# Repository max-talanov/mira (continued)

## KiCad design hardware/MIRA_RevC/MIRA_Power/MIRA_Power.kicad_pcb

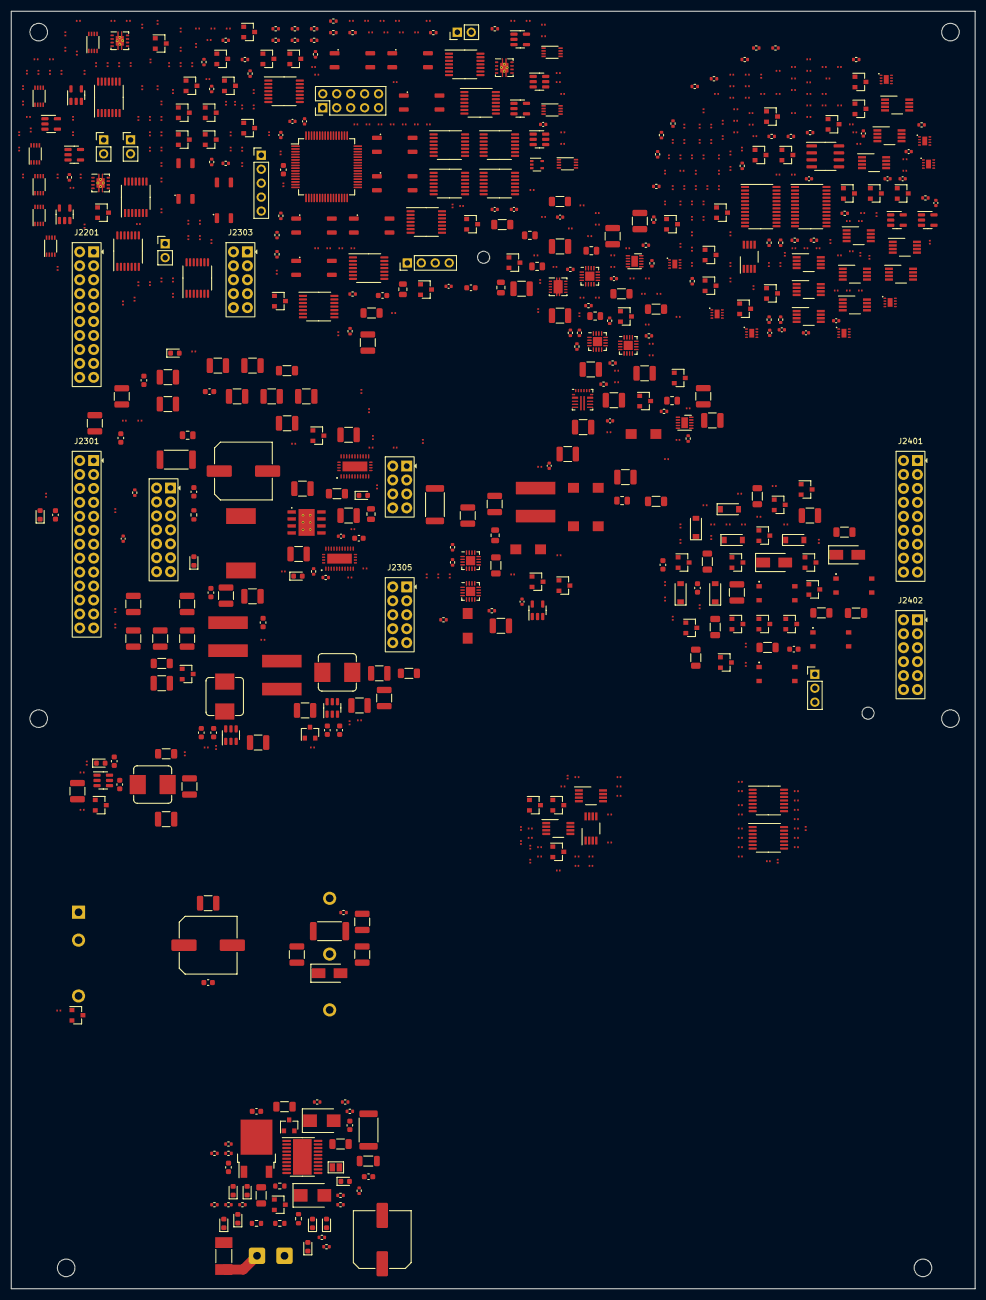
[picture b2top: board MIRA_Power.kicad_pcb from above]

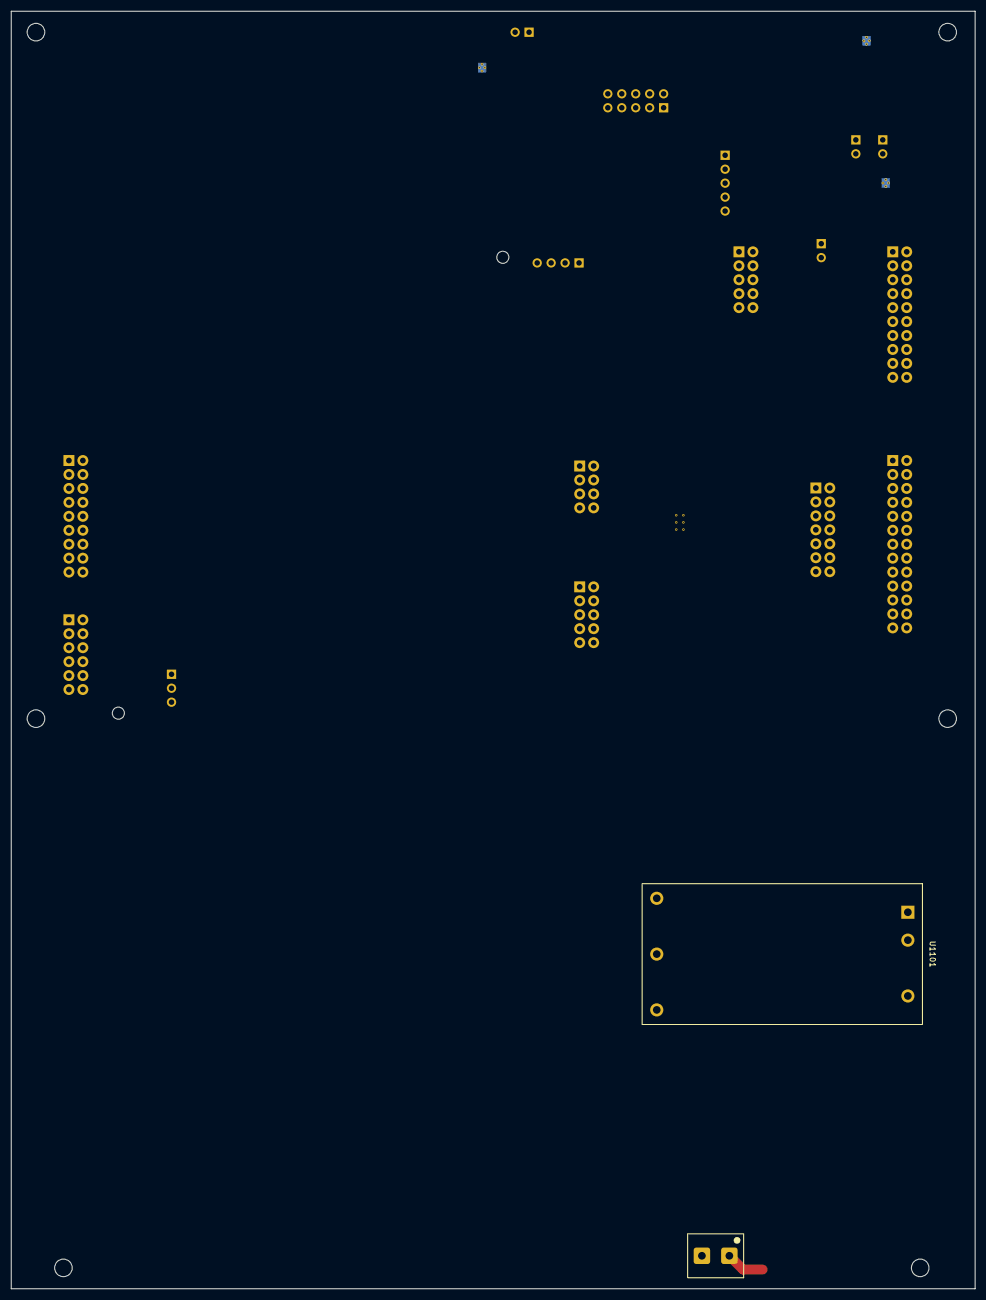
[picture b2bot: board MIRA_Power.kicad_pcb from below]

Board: 4 copper layers, 175.5 x 232.6 mm, 801 parts (2 on the bottom side), 403 nets.

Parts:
C301, C303, C304, C307, C501, C503, C604, C605, C705, C813, C902, C903, C1005, C1006, C1102, C1901, C2001, C2101: 100n; C_0603_1608Metric
C302, C305, C306: 1u; C_1206_3216Metric
C308, C1010, C1106: 100u; C_Elec_10x10.2
C502, C601, C707, C708, C802, C808, C904, C1004, C1008, C1101, C1903, C2003: 4.7u; C_1210_3225Metric
C504, C505, C602, C603, C702, C709, C710, C711, C712, C713, C804, C806, C807, C809, C812, C814, C901, C905, C1301, C1303, C1304, C1306, C1307, C1308, C1309, C1311, C1401, C1408, C1412, C1503, C1602, C1701, C1703, C1706, C1708: 47u; C_1210_3225Metric
C701, C811, C2603: 1u; C_0402_1005Metric
C703, C805, C1305: 22n; C_0201_Murata_GRM03_Gap0.25
C704, C803: 2.2u; C_0603_1608Metric
C706, C801: 150p; C_0201_Murata_GRM03_Gap0.25
C714, C810: 470n; C_0603_1608Metric
C1001: 220n; C_0805_2012Metric
C1002, C1003, C1007: 10u; C_1210_3225Metric
C1009: 1u; C_0805_2012Metric
C1103, C1104, C1105: 22u; C_1210_3225Metric
C1302, C1511, C2601: 4.7u; C_0603_1608Metric
C1310, C1312, C1403, C1405, C1409, C1501, C1601, C2201, C2901, C2902, C3701, C4401, C4901, C4902, C4903, C4904, C5001, C5002, C5003, C5004, C5101: 100n; C_0402_1005Metric
C1402, C1406, C1411, C1504, C1603, C1702, C1705, C2703, C3801, C3803, C3804, C3805, C4101, C4202, C4501, C4502, C4504, C4506, C4508, C4509, C4511, C4512, C4601, C4602, C4603, C4604, C4605, C4608, C4701, C4702, C4704, C4705, C4707, C4708, C4711, C4712, C4801, C4802, C4803, C4805, C4806, C4809, C4810, C4812: 10n; C_0201_Murata_GRM03_Gap0.25
C1404, C1407, C1410, C1502, C1505, C1506, C1507, C1508, C1604: 10u; C_0805_2012Metric
C1509, C1510, C1704, C1707, C2602, C2604, C2605, C2701, C2702, C2801, C2802, C2803, C2804, C2805, C3001, C3002, C3003, C3101, C3102, C3103, C3201, C3202, C3301, C3302, C3401, C3402, C3403, C3404, C3405, C3406, C3407, C3408, C3802, C3901, C3902, C3903, C4001, C4002, C4003, C4102, C4201, C4402, C4403, C4404, C4503, C4505, C4507, C4510, C4606, C4607, C4609, C4703, C4706, C4709, C4710, C4804, C4807, C4808, C4811, C5201, C5202, C5303: 100n; C_0201_Murata_GRM03_Gap0.25
C1902, C2002: 47n; C_1206_3216Metric
C5301, C5302: 1n; C_0201_Murata_GRM03_Gap0.25
D301, D305, D310, D501, D601, D701, D801, D901, D1001: Green LED; LED_0603_1608Metric
D302, D304, D308: Red LED; LED_0603_1608Metric
D303, D307: CD0603-B0240R; D_0603_1608Metric
D306: SMBJ36CA; D_SMB
D309: STPS3H100U; D_SMB
D1101: SS14-13-F; D_SMA
D1901, D2004: SS14 OUTPUT CLAMP; D_SMA
D1902, D1903, D1904, D2001, D2002, D2003: 10V G-S CLAMP; D_SOD-123
D2101: BAT54S ADC CLAMP; SOT-23
D2701: BAT54A; SOT-23
D4201, D4401, D4402, D4403, D4501, D4502, D4503, D4504, D4601, D4602, D4603, D4701, D4702, D4703, D4704, D4801, D4802, D4803, D4804: BAT54S; SOT-23
F301: 5A / 125V; Fuse_Littelfuse_0451_2410_Mfr
H9101, H9102, H9103, H9104, H9301, H9302: M3 support 12mm hardware TBD
H9201, H9202: M2 support12mm under module
J301: DG126-5.0-02P-14; TerminalBlock_Degson_DG126-5.0-02P-14_1x02_P5.00mm
J2101: PROGRAM +/-15V; PinHeader_1x03_P2.54mm_Vertical
J2201: SSW-110-01-S-D; Samtec_SSW-110-01-S-D_2x10_P2.54mm_Vertical
J2301: SSW-113-01-S-D; Samtec_SSW-113-01-S-D_2x13_P2.54mm_Vertical
J2302: SSW-107-01-S-D; Samtec_SSW-107-01-S-D_2x07_P2.54mm_Vertical
J2303, J2305: SSW-105-01-S-D; Samtec_SSW-105-01-S-D_2x05_P2.54mm_Vertical
J2304: SSW-104-01-S-D; Samtec_SSW-104-01-S-D_2x04_P2.54mm_Vertical
J2401: SSW-109-01-S-D; Samtec_SSW-109-01-S-D_2x09_P2.54mm_Vertical
J2402: SSW-106-01-S-D; Samtec_SSW-106-01-S-D_2x06_P2.54mm_Vertical
J2701: HOST MANUAL RESET CONTACT; PinHeader_1x02_P2.54mm_Vertical
J2702: PM MANUAL RESET CONTACT; PinHeader_1x02_P2.54mm_Vertical
J3101: MATRIX STOP - CLOSE TO TRIP; PinHeader_1x02_P2.54mm_Vertical
J3102: GLOBAL STOP - CLOSE TO TRIP; PinHeader_1x02_P2.54mm_Vertical
J3103: MATRIX HARDWARE INTERLOCK - AON LOGIC; PinHeader_1x04_P2.54mm_Vertical
J4201: PM SWD - VTREF ONLY; PinHeader_1x05_P2.54mm_Vertical
J4202: MAIN CONTROLLER UART / WATCHDOG / STATUS; PinHeader_2x05_P2.54mm_Vertical
JP301: SolderJumper_2_Open; SolderJumper-2_P1.3mm_Open_Pad1.0x1.5mm
L301: 120R @ 100MHz / 6A; L_1206_3216Metric
L501, L601, L901: 33uH; L_Bourns_SRP7028A_7.3x6.6mm
L701, L801: 6.8uH; L_Bourns_SRP7030CA_7.8x7.6mm
L1001: 47u; L_Wurth_7447709101_12x12mm
L1301: 1u; L_Bourns_SRP7030CA_7.8x7.6mm
L1401, L1402, L1403, L1501, L1601: 2.2u; L_Bourns_SRP5030TA_5.7x5.2mm
Q301, Q302, Q601, Q701, Q801, Q901, Q1101, Q1301, Q1401, Q1402, Q1403, Q1501, Q1601, Q1701, Q1702, Q3101, Q3102: BSS138N; SOT-23
Q303: IRFR3410; TO-252-2
Q1901, Q1904, Q1906, Q2001: AO3401A; SOT-23
Q1902, Q1903, Q1905, Q1907, Q2002, Q2003, Q2004, Q3501, Q3502, Q3503, Q3504, Q3505, Q3601, Q3602, Q3603, Q3604, Q3605: AO3400A; SOT-23
R301, R303, R305, R317, R1004: 10k; R_0603_1608Metric
R302, R309, R311, R4402, R4404, R4408: 10k; R_0402_1005Metric
R304, R3502, R3504, R3506, R3508, R3510, R3602, R3604, R3606, R3608, R3610: 22k; R_0402_1005Metric
R306: 24k; R_0402_1005Metric
R307, R314: 150k; R_0402_1005Metric
R308: 16.2k; R_0402_1005Metric
R310, R313: 180k; R_0402_1005Metric
R312: 12.1k; R_0402_1005Metric
R315: 4.02k; R_0402_1005Metric
R316, R318, R1001, R1005, R1102, R3701, R4409, R4901, R4902, R4903, R4904, R4905, R4906, R4907, R4908, R5001, R5002, R5003, R5004, R5005, R5006, R5007, R5101: 100k; R_0402_1005Metric
R319: 20m / 1W; R_2512_6332Metric
R501: 62k; R_0201_Panasonic_ERJ1G_Gap0.30
R502, R601, R703, R801, R901, R4203, R4205, R4511, R4512, R4514, R4516, R4601, R4604, R4611, R4701, R4711, R4714, R4715, R4802, R4807, R4812, R4814: 1k; R_0201_Panasonic_ERJ1G_Gap0.30
R503: 0.1R; R_1206_3216Metric
R504, R603, R905: 20k; R_0201_Panasonic_ERJ1G_Gap0.30
R602, R702, R704, R803, R806, R903, R1103, R1305, R1403, R1412, R1414, R1502, R1508, R1605, R1705, R1712, R1901, R1904, R1905, R1908, R2004, R2007, R2008, R2201, R2701, R2706, R2804, R2901, R2902, R2903, R3002, R3004, R3102, R3103, R3104, R3107, R3201, R3202, R3203, R3204, R3205, R3206, R3207, R3208, R3209, R3210, R3211, R3212, R3213, R3214, R3215, R3216, R3301, R3302, R3303, R3304, R3305, R3306, R3307, R3308, R3309, R3310, R3311, R3312, R3313, R3314, R4202, R4206, R4207, R5301, R5304, R5306, R5307, R5308: 100k; R_0201_Panasonic_ERJ1G_Gap0.30
R604, R904, R1703, R1710: 0.05R; R_1206_3216Metric
R605: 105k; R_0201_Panasonic_ERJ1G_Gap0.30
R701, R802, R1301, R1303, R1307, R1402, R1406, R1409, R1411, R1413, R1416, R1505, R1506, R1509, R1603, R1604, R1701, R1706, R1709, R1711, R2101, R2102, R2702, R2703, R2704, R2705, R2707, R2708, R2709, R2801, R2802, R2803, R3101, R3105, R3106, R3413, R3416, R3802, R3803, R3805, R3808, R3809, R3810, R3811, R3812, R4101, R4501, R4502, R4503, R4506, R4507, R4508, R4509, R4510, R4513, R4515, R4602, R4603, R4605, R4607, R4608, R4609, R4612, R4702, R4703, R4704, R4705, R4706, R4707, R4708, R4709, R4710, R4713, R4716, R4801, R4803, R4804, R4805, R4806, R4808, R4809, R4810, R4811, R4813, R4816, R5302: 10k; R_0201_Panasonic_ERJ1G_Gap0.30
R705: 43.2k; R_0201_Panasonic_ERJ1G_Gap0.30
R706, R804, R1504: 0.01R; R_1206_3216Metric
R805: 22.1k; R_0201_Panasonic_ERJ1G_Gap0.30
R902: 130k; R_0201_Panasonic_ERJ1G_Gap0.30
R1002, R1101: 0.1R; R_2512_6332Metric
R1003: 7.15k; R_0402_1005Metric
R1302: 15.0k; R_0402_1005Metric
R1304: 0.002R; R_2512_6332Metric
R1306: 10.2k; R_0402_1005Metric
R1308: 200k; R_0201_Panasonic_ERJ1G_Gap0.30
R1309, R5303, R5305: 100; R_0201_Panasonic_ERJ1G_Gap0.30
R1401: 20.0k; R_0402_1005Metric
R1404, R1408, R1418, R1501, R1601, R1708: 16.0k; R_0402_1005Metric
R1405, R1410, R1415, R1606: 0.02R; R_1206_3216Metric
R1407: 34.0k; R_0402_1005Metric
R1417, R1707: 49.9k; R_0402_1005Metric
R1503: 11.0k; R_0402_1005Metric
R1507, R1510, R4102, R4403, R4405, R4406: 10.0k; R_0402_1005Metric
R1511: 0R; R_0201_Panasonic_ERJ1G_Gap0.30
R1602: 20k; R_0402_1005Metric
R1702: 2.00k; R_0402_1005Metric
R1704: 10.5k; R_0402_1005Metric
R1902, R1907, R1909, R2006, R2009, R2011: 680R; R_1206_3216Metric
R1903, R2002, R2003, R2005: 300; R_0201_Panasonic_ERJ1G_Gap0.30
R1906, R2010: 330k; R_0201_Panasonic_ERJ1G_Gap0.30
R1910, R2001: 1M; R_0201_Panasonic_ERJ1G_Gap0.30
R2103, R3406, R4606: 47k; R_0201_Panasonic_ERJ1G_Gap0.30
R3001: 590k; R_0201_Panasonic_ERJ1G_Gap0.30
R3003: 150k; R_0201_Panasonic_ERJ1G_Gap0.30
R3401, R3402, R3403, R3404, R3405, R3407, R3408, R3409, R3410, R3411, R3412, R3414, R3415: 220k; R_0201_Panasonic_ERJ1G_Gap0.30
R3501, R3503, R3505, R3507, R3509, R3601, R3603, R3605, R3607, R3609: 270; R_0402_1005Metric
R3702: 1k; R_0402_1005Metric
R3801: 4.7k; R_0201_Panasonic_ERJ1G_Gap0.30
R3804: 3.9k; R_0201_Panasonic_ERJ1G_Gap0.30
R3806: 15k; R_0201_Panasonic_ERJ1G_Gap0.30
R3807: 2.2k; R_0201_Panasonic_ERJ1G_Gap0.30
R4103: 2.74k; R_0402_1005Metric
R4201, R4204: 33; R_0201_Panasonic_ERJ1G_Gap0.30
R4401, R4407: 200k; R_0402_1005Metric
R4504, R4505: 75k; R_0201_Panasonic_ERJ1G_Gap0.30
R4610: 30.1k; R_0201_Panasonic_ERJ1G_Gap0.30
R4712: 7.50k; R_0201_Panasonic_ERJ1G_Gap0.30
R4815: 13.7k; R_0201_Panasonic_ERJ1G_Gap0.30
U301: TPS26631PWPR; HTSSOP-20-1EP_4.4x6.5mm_P0.65mm_EP3.4x6.5mm_Mask2.96x2.96mm
U501, U601, U901: LMR51610XDBVR; SOT-23-6
U701, U801: LM76005RNPR; TI_LM76005_RNP0030G
U1001: LMR36520FADDAR; TI_DDA0008B
U1101: ECB40W18-72S15N; Cincon_ECB40W18_no_bus
U1301: TPS568215RNNR; Texas_RNN0018A
U1401, U1402, U1403, U1501, U1601: TPS62130ARGTR; VQFN-16-1EP_3x3mm_P0.5mm_EP1.68x1.68mm
U1502: TPS51200DRCR; Texas_DRC0010J
U1701, U1702: TPS7A9101DSKR; WSON-10-1EP_2.5x2.5mm_P0.5mm_EP1.2x2mm
U1901, U2001, U2002, U2003: LTV-356T-A; LTV356T_SOP4_P2.54mm_Mfr
U2201, U2901, U2902, U5101: 74LVC1G17GV,125; SOT-23-5
U2601: STM32G0B1RBT6; LQFP-64_10x10mm_P0.5mm
U2701, U2702, U2801: TPS3851H33EDRBR; Texas_DRB0008A
U2802: 74LVC1G14GV; SOT-23-5
U2803, U3003: 74LVC1G08GV; SOT-23-5
U2804: SN74LVC1G74DCUR; VSSOP-8_2.3x2mm_P0.5mm
U2805: SN74LVC1G07DBVR; SOT-23-5
U3001: TPS3808G01DBVR; SOT-23-6
U3002: 74AUP1G34GW; SOT-353_SC-70-5
U3101, U3103, U3901, U3902, U3903, U4001, U4002, U4003: SN74HCS21PWR; TSSOP-14_4.4x5mm_P0.65mm
U3102: SN74HC74PWR; TSSOP-14_4.4x5mm_P0.65mm
U3201, U3202, U3301, U3302: SN74HC08PWR; TSSOP-14_4.4x5mm_P0.65mm
U3401, U3402, U3403, U3404, U3405, U3406, U3407, U3408: 74AUP2G126DC; VSSOP-8_2.3x2mm_P0.5mm
U3501, U3502, U3503, U3504, U3505, U3601, U3602, U3603, U3604, U3605: TLP172GM(TPR,E); SO6_4Pin_Toshiba_11-4M1S
U3701: SN74LVC1G11; SOT-23-6
U3801, U4101: TLV1704AIPWR; TSSOP-14_4.4x5mm_P0.65mm
U4201: 74LVC125APW,118; TSSOP-14_4.4x5mm_P0.65mm
U4401: OPA2991IDR; SOIC-8_3.9x4.9mm_P1.27mm
U4501, U4502, U4504, U4601, U4602, U4603, U4702, U4703, U4704, U4801, U4802, U4804: INA301A1IDGKR; VSSOP-8_3.0x3.0mm_P0.65mm
U4503: INA293A1IDBVR; SOT-23-5
U4701, U4803: INA301A2IDGKR; VSSOP-8_3.0x3.0mm_P0.65mm
U4901, U4902, U4903, U4904, U5001, U5002, U5003, U5004: TMUX2821DSGR; WSON-8_2x2mm_P0.5mm_EP0.9x1.6mm
U5201, U5202: CD74HC4067PWR; TSSOP-24_4.4x7.8mm_P0.65mm
U5301: TLV9002IDGKR; VSSOP-8_3.0x3.0mm_P0.65mm

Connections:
+24V_FUSED: C301.2, C305.1, D306.2 (A2), F301.2, Q302.2 (S), Q303.3 (S), R304.1, R305.2, R313.2, U301.6 (IN_SYS)
+24V_RAW: F301.1, J301.1, R301.2, R303.1
/Power Distribution/Power Sequencing/Command Ready/CMD_GROUP_0: U4001.1 (1A), U4002.6 (1Y)
/Power Distribution/Power Sequencing/Command Ready/CMD_GROUP_1: U4001.2 (1B), U4002.8 (2Y)
/Power Distribution/Power Sequencing/Command Ready/CMD_GROUP_2: U4001.4 (1C), U4003.6 (1Y)
/Power Distribution/Power Sequencing/Command Ready/CMD_GROUP_3: U4001.5 (1D), U4003.8 (2Y)
/Power Distribution/Power Sequencing/Permit Interlocks/INPUT_AON_OK: U3101.6 (1Y), U3101.9 (2A)
/Power Distribution/Power Sequencing/Permit Interlocks/MATRIX_BASE_OK: U3103.6 (1Y), U3103.9 (2A)
/Power Distribution/Power Sequencing/Permit Interlocks/MATRIX_CLEAR_N: U3102.13 (2CLR_N), U3103.8 (2Y)
/Power Distribution/Power Sequencing/Rail Ready/PG_GROUP_0: U3901.6 (1Y), U3903.1 (1A)
/Power Distribution/Power Sequencing/Rail Ready/PG_GROUP_1: U3901.8 (2Y), U3903.2 (1B)
/Power Distribution/Power Sequencing/Rail Ready/PG_GROUP_2: U3902.6 (1Y), U3903.4 (1C)
/Power Distribution/Power Sequencing/Rail Ready/PG_GROUP_3: U3902.8 (2Y), U3903.5 (1D)
/Power Distribution/Primary Converters/AFE +15 V/CB_P15: C1006.1, U1001.7 (BOOT)
/Power Distribution/Primary Converters/AFE +15 V/FB_P15: R1003.1, R1005.2, U1001.5 (FB)
/Power Distribution/Primary Converters/AFE -15 V/N15_REMOTE_EN: Q1101.3 (D), U1101.6 (REMOTE)
/Power Distribution/Primary Converters/AON 3.3 V/AON_CB: C501.1, U501.1 (CB)
/Power Distribution/Primary Converters/AON 3.3 V/AON_FB: R501.1, R504.2, U501.3 (FB)
/Power Distribution/Primary Converters/Analog 6 V/ANA_CB: C903.1, U901.1 (CB)
/Power Distribution/Primary Converters/Analog 6 V/ANA_FB: R902.1, R905.2, U901.3 (FB)
/Power Distribution/Primary Converters/FPGA 5.5 V/FPGA_FB: C801.1, R805.2, R806.1, U801.12 (FB)
/Power Distribution/Primary Converters/FPGA 5.5 V/FPGA_SW: C810.2, L801.1, U801.1 (SW), U801.2 (SW), U801.3 (SW), U801.4 (SW), U801.5 (SW)
/Power Distribution/Primary Converters/System 3.3 V/SYS_FB: C706.1, R704.1, R705.2, U701.12 (FB)
/Power Distribution/Primary Converters/System 3.3 V/SYS_SW: C714.2, L701.1, U701.1 (SW), U701.2 (SW), U701.3 (SW), U701.4 (SW), U701.5 (SW)
/Power Distribution/Primary Converters/USB 5 V/USB_CB: C605.1, U601.1 (CB)
/Power Distribution/Primary Converters/USB 5 V/USB_FB: R603.2, R605.1, U601.3 (FB)
/Power Distribution/Secondary Converters/Analog LDO Rails/FB_ANA5: C1702.2, R1702.1, R1704.2, U1701.3 (FB)
/Power Distribution/Secondary Converters/Analog LDO Rails/FB_ANA33: C1705.2, R1707.2, R1708.1, U1702.3 (FB)
/Power Distribution/Secondary Converters/DDR Supply and Termination/FB_DDR: R1501.1, R1503.2, U1501.5 (FB)
/Power Distribution/Secondary Converters/FPGA Auxiliary Rails/FB_AUX18: R1401.2, R1404.1, U1401.5 (FB)
/Power Distribution/Secondary Converters/FPGA Auxiliary Rails/FB_AUX25: R1407.2, R1408.1, U1402.5 (FB)
/Power Distribution/Secondary Converters/FPGA Auxiliary Rails/FB_IO33: R1417.2, R1418.1, U1403.5 (FB)
/Power Distribution/Secondary Converters/FPGA Core 1 V/FB_CORE: R1302.1, R1306.2, U1301.13 (FB)
/Power Distribution/Secondary Converters/I-O 1.8 V/FB_IO18: R1601.1, R1602.2, U1601.5 (FB)
ADC_I: C5302.2, R5303.2, U2601.17 (PA0)
ADC_V: C5301.1, R5305.2, U2601.18 (PA1)
ADC_VTT: C4202.1, R4205.2, U5004.1 (S1)
ADC_VTT_SAFE: D4201.3 (K1/A2), R5007.1, U2601.19 (PA2), U5004.2 (D1)
ALL_COMMANDS_ON: U3103.4 (1C), U4001.6 (1Y)
ALL_RAILS_PG: U2601.3 (PC13), U3103.2 (1B), U3903.6 (1Y), U4201.9 (3A)
ALL_RAILS_PG_POWER: J2201.9, J4202.7, U4201.8 (3Y)
ANA3V3: J2402.7, R1709.1, R1710.2, R4813.2, U4802.7 (IN-)
ANA5: C1708.1, J2401.9, J2402.5, Q1702.3 (D), R1701.1, R1703.2, R4809.2, U1702.9 (IN), U1702.10 (IN), U4801.7 (IN-)
ANA5_RAW: C1702.1, C1703.1, R1703.1, R1704.1, U1701.1 (OUT), U1701.2 (OUT), U4801.8 (IN+)
ANA6: C1701.1, Q1701.3 (D), R901.1, R904.2, R4602.2, U1701.9 (IN), U1701.10 (IN), U4602.7 (IN-)
ANA33_RAW: C1705.1, C1706.1, R1707.1, R1710.1, U1702.1 (OUT), U1702.2 (OUT), U4802.8 (IN+)
ANA_RAW: C901.2, C905.2, L901.2, R902.2, R904.1, U4602.8 (IN+)
ANA_SW: C903.2, L901.1, U901.6 (SW)
AON: C1511.1, C2201.1, C2601.1, C2602.1, C2603.1, C2604.1, C2605.1, C2701.1, C2801.1, C2802.1, C2803.1, C2804.1, C2805.1, C2901.1, C2902.1, C3001.1, C3002.1, C3003.1, C3101.1, C3102.1, C3103.1, C3201.1, C3202.1, C3301.1, C3302.1, C3401.1, C3402.1, C3403.1, C3404.1, C3405.1, C3406.1, C3407.1, C3408.1, C3701.1, C3802.1, C3901.1, C3902.1, C3903.1, C4001.1, C4002.1, C4003.1, C4102.1, C4402.1, C4503.1, C4505.1, C4507.1, C4510.1, C4606.1, C4607.1, C4609.1, C4703.1, C4706.1, C4709.1, C4710.1, C4804.1, C4807.1, C4808.1, C4811.1, C4901.1, C4902.1, C4903.1, C4904.1, C5001.1, C5002.1, C5003.1, C5004.1, C5101.1, C5201.1, C5202.1, C5303.1, D2101.2 (K), D4201.2 (K), D4401.2 (K), D4402.2 (K), D4403.2 (K), D4501.2 (K), D4502.2 (K), D4503.2 (K), D4504.2 (K), D4601.2 (K), D4602.2 (K), D4603.2 (K), D4701.2 (K), D4702.2 (K), D4703.2 (K), D4704.2 (K), D4801.2 (K), D4802.2 (K), D4803.2 (K), D4804.2 (K), J2201.19, J2303.7, J2402.11, J3103.3, J4201.1, R309.1, R311.2, R502.1, R503.2, R701.1, R802.1, R1301.2, R1406.2, R1411.2, R1416.2, R1506.2, R1509.2, R1604.2, R1706.2, R1711.2, R1903.1, R2002.1, R2003.1, R2005.1, R2010.1, R2702.2, R2704.2, R2705.2, R2708.2, R2709.2, R2801.1, R2802.1, R2803.1, R3001.1, R3003.1, R3004.1, R3101.2, R3105.2, R3106.2, R3501.1, R3503.1, R3505.1, R3507.1, R3509.1, R3601.1, R3603.1, R3605.1, R3607.1, R3609.1, R3801.1, R3802.2, R3804.1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
AON_MON_ENABLE: R5101.1, U4901.3 (SEL2), U4901.7 (SEL1), U4902.3 (SEL2), U4902.7 (SEL1), U4903.3 (SEL2), U4903.7 (SEL1), U4904.3 (SEL2), U4904.7 (SEL1), U5001.3 (SEL2), U5001.7 (SEL1), U5002.3 (SEL2), U5002.7 (SEL1), U5003.3 (SEL2), U5003.7 (SEL1), U5004.7 (SEL1), U5101.4 (Y)
AON_RAW: C504.2, C505.2, L501.2, R501.2, R503.1, U4504.8 (IN+)
AON_RESET_N: D2701.1 (K1), R2704.1, U2702.8 (RESET_N), U3101.1 (1A)
AON_SW: C501.2, L501.1, U501.6 (SW)
AUX1V8: J2301.19, J2301.21, R1402.1, R1405.2, R4707.2, U4703.7 (IN-)
AUX2V5: R1409.1, R1410.2, R4705.2, U4704.7 (IN-)
AUX18_RAW: C1401.1, L1401.2, R1401.1, R1405.1, U1401.7 (FSW), U1401.14 (VOS), U4703.8 (IN+)
AUX25_RAW: C1408.1, L1402.2, R1407.1, R1410.1, U1402.7 (FSW), U1402.14 (VOS), U4704.8 (IN+)
BUS24: C502.1, C503.1, C601.1, C604.1, C705.2, C707.2, C708.2, C802.2, C808.2, C813.2, C902.1, C904.1, C1001.1, C1004.1, C1008.1, C1101.1, C1102.1, C1106.1, Q601.3 (D), Q701.3 (D), Q801.3 (D), Q901.3 (D), R317.2, R318.2, R319.2, R4504.2, U501.4 (EN), U501.5 (VIN), U601.5 (VIN), U701.20 (PVIN), U701.21 (PVIN), U701.22 (PVIN), U801.20 (PVIN), U801.21 (PVIN), U801.22 (PVIN), U901.5 (VIN), U1001.2 (VIN), U1101.1 (+VIN), U3501.6 (SW1), U3502.6 (SW1), U3503.6 (SW1), U3504.6 (SW1), U3505.6 (SW1), U4503.4 (IN-)
BUS24_PRE_SHUNT: C306.2, C307.2, C308.1, L301.2, R319.1, U4503.3 (IN+)
CMD_ANA: Q901.1 (G), R3404.1, U3402.3 (2Y), U4002.5 (1D)
CMD_ANA5: Q1701.1 (G), R3414.1, U3407.3 (2Y), U4003.10 (2B)
CMD_ANA5_RAW: R3307.1, U3301.6 (2Y), U3407.5 (2A)
CMD_ANA33: Q1702.1 (G), R3415.1, U3408.6 (1Y), U4003.12 (2C)
CMD_ANA33_RAW: R3309.1, U3301.8 (3Y), U3408.2 (1A)
CMD_ANA_RAW: R3205.2, U3201.11 (4Y), U3402.5 (2A)
CMD_AUX18: Q1401.1 (G), R3408.1, U3404.3 (2Y), U4002.13 (2D)
CMD_AUX18_RAW: R3213.2, U3202.11 (4Y), U3404.5 (2A)
CMD_AUX25: Q1402.1 (G), R3409.1, U3405.6 (1Y), U4003.1 (1A)
CMD_AUX25_RAW: R3304.1, U3302.3 (1Y), U3405.2 (1A)
CMD_CORE: Q1301.1 (G), R3407.1, U3404.6 (1Y), U4002.12 (2C)
CMD_CORE_RAW: R3208.1, U3202.8 (3Y), U3404.2 (1A)
CMD_DDR: Q1501.1 (G), R3411.1, U3406.6 (1Y), U4003.4 (1C)
CMD_DDR_RAW: R3311.1, U3302.8 (3Y), U3406.2 (1A)
CMD_FPGA: Q801.1 (G), R3403.1, U3402.6 (1Y), U4002.4 (1C)
CMD_FPGA_RAW: R3209.1, U3201.8 (3Y), U3402.2 (1A)
CMD_IO18: Q1601.1 (G), R3412.1, U3406.3 (2Y), U4003.5 (1D)
CMD_IO18_RAW: R3303.2, U3302.11 (4Y), U3406.5 (2A)
CMD_IO33: Q1403.1 (G), R3410.1, U3405.3 (2Y), U4003.2 (1B)
CMD_IO33_RAW: R3305.1, U3302.6 (2Y), U3405.5 (2A)
CMD_N15: Q1101.1 (G), R1103.1, R3406.1, U3403.3 (2Y), U4002.10 (2B)
CMD_N15_RAW: R3210.1, U3202.6 (2Y), U3403.5 (2A)
CMD_P15: Q3505.1 (G), R3405.1, U3403.6 (1Y), U4002.9 (2A)
CMD_P15_RAW: R3211.1, U3202.3 (1Y), U3403.2 (1A)
CMD_SYS: Q701.1 (G), R3402.1, U3401.3 (2Y), U4002.1 (1A), U4002.2 (1B)
CMD_SYS_RAW: R3206.1, U3201.6 (2Y), U3401.5 (2A)
CMD_USB: Q601.1 (G), R3401.1, U3401.6 (1Y)
CMD_USB_RAW: R3207.1, U3201.3 (1Y), U3401.2 (1A)
CMD_VTT: R1511.1, R3413.1, U3407.6 (1Y), U4003.9 (2A)
CMD_VTT_RAW: R3306.1, U3301.3 (1Y), U3407.2 (1A)
CORE1V0: J2301.1, J2301.3, J2301.5, J2301.7, J2301.9, J2301.11, J2301.13, J2301.15, R1304.2, R1307.1, R4702.2, U4701.7 (IN-)
CORE_RAW: C1301.1, C1303.1, C1304.2, C1308.2, C1309.1, C1311.2, L1301.2, R1304.1, R1309.1, U4701.8 (IN+)
CORE_SENSE_P: J2301.17, R1306.1, R1309.2
DDR1V35: C1506.1, J2302.1, J2302.3, J2302.5, R1504.2, R1505.1, R1510.1, R4810.2, U1502.2 (VLDOIN), U4803.7 (IN-)
DDR_RAW: C1503.1, L1501.2, R1503.1, R1504.1, U1501.7 (FSW), U1501.14 (VOS), U4803.8 (IN+)
DDR_VREF: C1509.1, J2302.11, U1502.6 (REFOUT)
EFUSE_OUT: C303.2, D309.1 (K), L301.1, R307.1, U301.18 (OUT), U301.19 (OUT), U301.20 (OUT)
EFUSE_OVP: R308.1, R312.2, U301.8 (OVP)
EFUSE_UVLO: R308.2, R310.1, U301.7 (UVLO)
EN_ANA: Q901.2 (S), Q3504.1 (G), R903.2
EN_ANA5: Q1701.2 (S), R1705.1, U1701.7 (EN)
EN_ANA33: Q1702.2 (S), R1712.1, U1702.7 (EN)
EN_ANA_LED_A: R3507.2, U3504.1 (A)
EN_ANA_LED_K: Q3504.3 (D), U3504.3 (K)
EN_ANA_VIN: R3508.1, U901.4 (EN), U3504.4 (SW2)
EN_AUX18: Q1401.2 (S), Q3601.1 (G), R1403.1, U3701.6 (C)
EN_AUX18_LED_A: R3601.2, U3601.1 (A)
EN_AUX18_LED_K: Q3601.3 (D), U3601.3 (K)
EN_AUX18_VIN: R3602.1, U1401.13 (EN), U3601.4 (SW2)
EN_AUX25: Q1402.2 (S), Q3602.1 (G), R1412.1
EN_AUX25_LED_A: R3603.2, U3602.1 (A)
EN_AUX25_LED_K: Q3602.3 (D), U3602.3 (K)
EN_AUX25_VIN: R3604.1, U1402.13 (EN), U3602.4 (SW2)
EN_CORE: Q1301.2 (S), R1305.1, U1301.15 (EN)
EN_DDR: Q1501.2 (S), Q3604.1 (G), R1502.1
EN_DDR_LED_A: R3607.2, U3604.1 (A)
EN_DDR_LED_K: Q3604.3 (D), U3604.3 (K)
EN_DDR_VIN: R3608.1, U1501.13 (EN), U3604.4 (SW2)
EN_FPGA: Q801.2 (S), Q3503.1 (G), R803.2
EN_FPGA_LED_A: R3505.2, U3503.1 (A)
EN_FPGA_LED_K: Q3503.3 (D), U3503.3 (K)
EN_FPGA_VIN: R3506.1, U801.18 (EN), U3503.4 (SW2)
EN_IO18: Q1601.2 (S), Q3605.1 (G), R1605.1
EN_IO18_LED_A: R3609.2, U3605.1 (A)
EN_IO18_LED_K: Q3605.3 (D), U3605.3 (K)
EN_IO18_VIN: R3610.1, U1601.13 (EN), U3605.4 (SW2)
EN_IO33: Q1403.2 (S), R1414.1, U3701.1 (A)
EN_IO33_LED_A: R3605.2, U3603.1 (A)
EN_IO33_LED_K: Q3603.3 (D), U3603.3 (K)
EN_IO33_QUAL: Q3603.1 (G), R3701.1, U3701.4 (Y)
EN_IO33_VIN: R3606.1, U1403.13 (EN), U3603.4 (SW2)
EN_P15_LED_A: R3509.2, U3505.1 (A)
EN_P15_LED_K: Q3505.3 (D), U3505.3 (K)
EN_P15_VIN: R3510.1, U1001.3 (EN), U3505.4 (SW2)
EN_REQ_ANA: R3204.2, U2601.23 (PA6), U3201.13 (4B)
EN_REQ_ANA5: R3312.1, U2601.33 (PB13), U3301.5 (2B)
EN_REQ_ANA33: R3314.1, U2601.34 (PB14), U3301.10 (3B)
EN_REQ_AUX18: R3216.2, U2601.27 (PB0), U3202.13 (4B)
EN_REQ_AUX25: R3308.1, U2601.28 (PB1), U3302.2 (1B)
EN_REQ_CORE: R3215.1, U2601.26 (PC5), U3202.10 (3B)
EN_REQ_DDR: R3301.1, U2601.30 (PB10), U3302.10 (3B)
EN_REQ_FPGA: R3201.1, U2601.22 (PA5), U3201.10 (3B)
EN_REQ_IO18: R3310.2, U2601.31 (PB11), U3302.13 (4B)
EN_REQ_IO33: R3302.1, U2601.29 (PB2), U3302.5 (2B)
EN_REQ_N15: R3203.1, U2601.25 (PC4), U3202.5 (2B)
EN_REQ_P15: R3212.1, U2601.24 (PA7), U3202.2 (1B)
EN_REQ_SYS: R3214.1, U2601.21 (PA4), U3201.5 (2B)
EN_REQ_USB: R3202.1, U2601.10 (PF0), U3201.2 (1B)
EN_REQ_VTT: R3313.1, U2601.32 (PB12), U3301.2 (1B)
EN_SYS: Q701.2 (S), Q3502.1 (G), R702.2
EN_SYS_LED_A: R3503.2, U3502.1 (A)
EN_SYS_LED_K: Q3502.3 (D), U3502.3 (K)
EN_SYS_VIN: R3504.1, U701.18 (EN), U3502.4 (SW2)
EN_USB: Q601.2 (S), Q3501.1 (G), R602.2
EN_USB_LED_A: R3501.2, U3501.1 (A)
EN_USB_LED_K: Q3501.3 (D), U3501.3 (K)
EN_USB_VIN: R3502.1, U601.4 (EN), U3501.4 (SW2)
EN_VTT: R1508.1, R1511.2, U1502.7 (EN)
FLT_INPUT_N: D308.1 (K), R3105.1, U301.15 (FLT_N), U2601.43 (PA11), U3101.5 (1D)
FPGA5V5: C1306.2, C1307.1, C1310.1, C1403.1, C1404.1, C1405.1, C1407.1, C1409.1, C1410.1, C1501.1, C1502.1, C1601.1, C1604.1, Q1301.3 (D), Q1401.3 (D), Q1402.3 (D), Q1403.3 (D), Q1501.3 (D), Q1601.3 (D), R801.1, R804.2, R4607.2, U1301.2 (VIN), U1301.11 (VIN), U1401.10 (AVIN), U1401.11 (PVIN), U1401.12 (PVIN), U1402.10 (AVIN), U1402.11 (PVIN), U1402.12 (PVIN), U1403.10 (AVIN), U1403.11 (PVIN), U1403.12 (PVIN), U1501.10 (AVIN), U1501.11 (PVIN), U1501.12 (PVIN), U1601.10 (AVIN), U1601.11 (PVIN), U1601.12 (PVIN), U3601.6 (SW1), U3602.6 (SW1), U3603.6 (SW1), U3604.6 (SW1), U3605.6 (SW1), U4603.7 (IN-)
FPGA_BOOT: C810.1, U801.6 (BOOT)
FPGA_RAW: C801.2, C804.2, C806.2, C807.2, C809.2, C811.2, C812.2, C814.2, L801.2, R804.1, R806.2, U801.9 (BIAS), U4603.8 (IN+)
FPGA_SS: C805.2, U801.11 (SS/TRK)
FPGA_VCC: C803.2, U801.8 (VCC)
GLOBAL_CLEAR_N: U2601.4 (PC14), U3003.4 (Y), U3102.1 (1CLR_N)
GLOBAL_CLEAR_RAW_N: U3003.1 (A), U3101.8 (2Y)
GLOBAL_PWR_PERMIT: U2601.47 (PA15), U3102.5 (1Q), U3103.1 (1A), U3201.1 (1A), U3201.4 (2A), U3201.9 (3A), U3201.12 (4A), U3202.1 (1A), U3202.4 (2A), U3202.9 (3A), U3202.12 (4A), U3301.1 (1A), U3301.4 (2A), U3301.9 (3A), U3302.1 (1A), U3302.4 (2A), U3302.9 (3A), U3302.12 (4A), U4201.12 (4A)
GLOBAL_PWR_PERMIT_POWER: J2201.11, J4202.8, U4201.11 (4Y)
GND: C301.1, C302.2, C303.1, C304.2, C305.2, C306.1, C307.1, C308.2, C502.2, C503.2, C504.1, C505.1, C601.2, C602.1, C603.1, C604.2, C701.1, C702.1, C703.1, C704.1, C705.1, C707.1, C708.1, C709.1, C710.1, C711.1, C712.1, C713.1, C802.1, C803.1, C804.1, C805.1, C806.1, C807.1, C808.1, C809.1, C811.1, C812.1, C813.1, C814.1, C901.1, C902.2, C904.2, C905.1, C1001.2, C1002.2, C1003.2, C1004.2, C1005.2, C1007.2, C1008.2, C1009.2, C1010.2, C1101.2, C1102.2, C1103.1, C1104.1, C1105.1, C1106.2, C1301.2, C1302.2, C1303.2, C1304.1, C1305.2, C1306.1, C1307.2, C1308.1, C1309.2, C1310.2, C1311.1, C1401.2, C1402.2, C1403.2, C1404.2, C1405.2, C1406.2, C1407.2, C1408.2, C1409.2, C1410.2, C1411.2, C1412.2, C1501.2, C1502.2, C1503.2, C1504.2, C1505.2, C1506.2, C1507.2, C1508.2, C1509.2, C1510.2, C1511.2, C1601.2, C1602.2, C1603.2, C1604.2, C1701.2, C1703.2, C1704.2, C1706.2, C1707.2, C1708.2, C1901.2, C1903.2, C2001.2, C2003.2, C2101.2, C2201.2, C2601.2, C2602.2, C2603.2, C2604.2, C2605.2, C2701.2, C2702.2, C2703.2, C2801.2, C2802.2, C2803.2, C2804.2, C2805.2, C2901.2, C2902.2, C3001.2, C3002.2, C3003.2, C3101.2, C3102.2, C3103.2, C3201.2, C3202.2, C3301.2, C3302.2, C3401.2, C3402.2, C3403.2, C3404.2, C3405.2, C3406.2, C3407.2, C3408.2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
HOST_ALIVE: J2201.3, R2201.1, U2201.2 (A)
HOST_ALIVE_PM: U2201.4 (Y), U2601.11 (PF1), U2801.6 (WDI), U2802.2 (A)
HOST_RESET_AON_N: R2902.1, U2901.4 (Y), U3103.10 (2B)
HOST_RESET_N: J2201.15, R2707.1, R2901.1, U2701.8 (RESET_N), U2805.4 (Y_OD), U2901.2 (A)
HOST_UART_TX: J2201.5, J4202.4, R4203.1
HOST_UART_TX_RAW: R4202.1, R4203.2, U2902.2 (A)
HOST_WDI: J2201.1, J4202.5, R2701.1, U2701.6 (WDI)
HOST_WDO_N: R2709.1, U2601.49 (PC9), U2701.7 (WDO_N), U2805.2 (A), U3103.5 (1D)
IO1V8: J2305.1, J2305.3, R1603.1, R1606.2, R4805.2, U4804.7 (IN-)
IO3V3: J2301.23, J2301.25, J2302.13, J2303.9, J2304.1, J2304.3, J2305.5, J2305.7, J2305.9, J2401.11, J2401.17, J2402.9, R1413.1, R1415.2, R3702.1, R4708.2, U4702.7 (IN-)
IO18_RAW: C1602.1, L1601.2, R1602.1, R1606.1, U1601.7 (FSW), U1601.14 (VOS), U4804.8 (IN+)
IO33_RAW: C1412.1, L1403.2, R1415.1, R1417.1, U1403.7 (FSW), U1403.14 (VOS), U4702.8 (IN+)
LINK_CLEAR_N: U2803.4 (Y), U2804.6 (CLR_N)
LINK_CWD: R2801.2, U2801.2 (CWD)
LINK_EDGE_H: U2802.4 (Y), U2804.1 (CLK)
LINK_READY_H: R2804.1, U2601.5 (PC15), U2804.5 (Q), U3103.13 (2D)
LINK_RESET_N: R2802.2, U2801.8 (RESET_N), U2803.1 (A)
LINK_WDO_N: R2803.2, U2801.7 (WDO_N), U2803.2 (B)
MATRIX_ARM_PULSE: R3103.1, U2601.14 (PC1), U3102.11 (2CLK)
MATRIX_INHIBIT_N: J2201.17, J3101.2, Q3102.3 (D), R3101.1, U3103.12 (2C)
MATRIX_KILL_GPIO: Q3102.1 (G), R3104.1, U2601.2 (PC12)
MATRIX_KILL_H: J3103.2, U3102.8 (2Q_N)
MATRIX_N_GATE: D2003.1 (K), Q2002.1 (G), Q2003.3 (D), Q2004.1 (G), R2001.1, R2006.1, U2002.3 (E)
MATRIX_N_SOURCE: D2002.2 (A), D2003.2 (A), Q2002.2 (S), Q2003.2 (S), Q2004.2 (S), R2001.2, U2003.3 (E)
MATRIX_OPTO_K: Q1902.3 (D), U1901.2 (K), U2001.2 (K), U2002.2 (K), U2003.2 (K)
MATRIX_PERMIT: J3103.1, Q1902.1 (G), Q1903.1 (G), Q1905.1 (G), R1904.1, R3416.1, U2601.48 (PC8), U3408.3 (2Y), U4201.5 (2A)
MATRIX_PERMIT_POWER: J2201.13, J4202.6, U4201.6 (2Y)
MATRIX_PERMIT_RAW: U3102.9 (2Q), U3408.5 (2A)
MATRIX_P_GATE: D1903.2 (A), Q1901.1 (G), Q1904.1 (G), Q1906.3 (D), R1902.1, R1906.1, R1910.1
MATRIX_P_SOURCE: D1903.1 (K), D1904.1 (K), Q1901.2 (S), Q1904.2 (S), Q1906.2 (S), R1910.2, U1901.4 (C)
MODE_CORE: R1303.1, R1308.2, U1301.18 (MODE)
MON_I_ANA5: C4806.1, R4802.1, U5202.17 (CH14)
MON_I_ANA6: C4602.1, R4601.1, U5202.4 (CH5)
MON_I_ANA33: C4805.1, R4807.1, U5202.16 (CH15)
MON_I_AON: C4501.1, R4511.1, U5202.8 (CH1)
MON_I_AUX18: C4705.1, R4715.1, U5202.22 (CH9)
MON_I_AUX25: C4701.1, R4714.1, U5202.21 (CH10)
MON_I_CORE: C4704.1, R4701.1, U5202.23 (CH8)
MON_I_DDR: C4810.1, R4812.1, U5202.19 (CH12)
MON_I_FPGA: C4601.1, R4611.1, U5202.5 (CH4)
MON_I_INPUT: C4506.1, R4512.2, U5202.9 (CH0)
MON_I_IO18: C4801.1, R4814.1, U5202.18 (CH13)
MON_I_IO33: C4707.1, R4711.1, U5202.20 (CH11)
MON_I_N15: C4403.1, D4401.3 (K1/A2), R4402.2, U5202.2 (CH7)
MON_I_P15: C4608.1, R4604.1, U5202.3 (CH6)
MON_I_SYS: C4509.1, R4514.1, U5202.6 (CH3)
MON_I_USB: C4502.1, R4516.1, U5202.7 (CH2)
MON_V_ANA5: C4802.1, R4809.1, R4816.1, U4901.5 (S2)
MON_V_ANA5_SAFE: D4802.3 (K1/A2), R4902.1, U4901.6 (D2), U5201.17 (CH14)
MON_V_ANA6: C4604.1, R4602.1, R4603.1, U3801.7 (IN2+), U4902.1 (S1)
MON_V_ANA6_SAFE: D4601.3 (K1/A2), R4903.1, U4902.2 (D1), U5201.4 (CH5)
MON_V_ANA33: C4803.1, R4804.1, R4813.1, U4901.1 (S1)
MON_V_ANA33_SAFE: D4803.3 (K1/A2), R4901.1, U4901.2 (D1), U5201.16 (CH15)
MON_V_AON: C4504.1, D4503.3 (K1/A2), R4501.1, R4502.1, U5201.8 (CH1)
MON_V_AUX18: C4712.1, R4703.1, R4707.1, U4902.5 (S2)
MON_V_AUX18_SAFE: D4701.3 (K1/A2), R4904.1, U4902.6 (D2), U5201.22 (CH9)
MON_V_AUX25: C4702.1, R4704.1, R4705.1, U4903.1 (S1)
MON_V_AUX25_SAFE: D4702.3 (K1/A2), R4905.1, U4903.2 (D1), U5201.21 (CH10)
MON_V_CORE: C4711.1, R4702.1, R4713.1, U4903.5 (S2)
MON_V_CORE_SAFE: D4704.3 (K1/A2), R4906.1, U4903.6 (D2), U5201.23 (CH8)
MON_V_DDR: C4809.1, R4810.1, R4811.1, U4904.1 (S1)
MON_V_DDR_SAFE: D4804.3 (K1/A2), R4907.1, U4904.2 (D1), U5201.19 (CH12)
MON_V_FPGA: C4605.1, R4607.1, R4608.1, U4904.5 (S2)
MON_V_FPGA_SAFE: D4603.3 (K1/A2), R4908.1, U4904.6 (D2), U5201.5 (CH4)
MON_V_INPUT: C4512.1, R4503.1, R4505.2, U5001.1 (S1)
MON_V_INPUT_SAFE: D4504.3 (K1/A2), R5001.1, U5001.2 (D1), U5201.9 (CH0)
MON_V_IO18: C4812.1, R4805.1, R4808.1, U5002.5 (S2)
MON_V_IO18_SAFE: D4801.3 (K1/A2), R5004.1, U5002.6 (D2), U5201.18 (CH13)
MON_V_IO33: C4708.1, R4708.1, R4710.1, U5001.5 (S2)
MON_V_IO33_SAFE: D4703.3 (K1/A2), R5002.1, U5001.6 (D2), U5201.20 (CH11)
MON_V_N15: C4404.1, D4403.3 (K1/A2), R4408.2, U3801.11 (IN4+), U5201.2 (CH7)
MON_V_P15: C4603.1, R4606.1, R4612.1, U3801.9 (IN3+), U5002.1 (S1)
MON_V_P15_SAFE: D4602.3 (K1/A2), R5003.1, U5002.2 (D1), U5201.3 (CH6)
MON_V_SYS: C4508.1, R4508.1, R4515.1, U5003.1 (S1)
MON_V_SYS_SAFE: D4501.3 (K1/A2), R5005.1, U5003.2 (D1), U5201.6 (CH3)
MON_V_USB: C4511.1, R4509.1, R4513.1, U3801.5 (IN1+), U5003.5 (S2)
MON_V_USB_SAFE: D4502.3 (K1/A2), R5006.1, U5003.6 (D2), U5201.7 (CH2)
MUX_A0: R5308.1, U2601.35 (PB15), U5201.10 (S0), U5202.10 (S0)
MUX_A1: R5304.1, U2601.36 (PA8), U5201.11 (S1), U5202.11 (S1)
MUX_A2: R5307.1, U2601.37 (PA9), U5201.14 (S2), U5202.14 (S2)
MUX_A3: R5306.1, U2601.38 (PC6), U5201.13 (S3), U5202.13 (S3)
MUX_DISABLE: R5301.1, U2601.39 (PC7), U5201.15 (DISABLE), U5202.15 (DISABLE)
MUX_I_COM: U5202.1 (COM), U5301.3 (IN+_A)
MUX_V_COM: U5201.1 (COM), U5301.5 (IN+_B)
N15: J2401.5, J2401.7, J2402.3, Q2002.3 (D), R1101.2, R1102.1, R4406.1, R4409.1
N15_RAW: C1103.2, C1104.2, C1105.2, C4401.1, D1101.2 (A), R1101.1, R4405.1, U1101.5 (-VOUT), U4401.4 (V-)
unnamed: C1312.1, L1301.1, U1301.6 (SW), U1301.7 (SW)
unnamed: C1902.1, R1902.2
unnamed: C2002.1, R2006.2
unnamed: D301.2 (A), D302.1 (K), R301.1
unnamed: D303.1 (K), D304.2 (A), Q301.3 (D), R303.2
unnamed: D305.2 (A), D307.1 (K), R305.1
unnamed: D308.2 (A), R309.2
unnamed: D310.2 (A), R317.1
unnamed: D501.1 (K), R502.2
unnamed: D601.1 (K), R601.2
unnamed: D701.2 (A), R703.2
unnamed: D801.2 (A), R801.2
unnamed: D901.1 (K), R901.2
unnamed: D1001.1 (K), R1004.1
unnamed: C1901.1, D1902.1 (K), Q1905.3 (D), Q1907.1 (G), R1908.2
unnamed: D1904.2 (A), Q1906.1 (G), R1905.1, U1901.3 (E)
unnamed: C2001.1, D2001.2 (A), Q2001.1 (G), R2007.2, U2001.3 (E)
unnamed: D2002.1 (K), Q2003.1 (G), R2008.1, U2003.4 (C)
unnamed: J2701.2, R2703.1, U2701.3 (MR_N)
unnamed: J2702.2, R2708.1, U2702.3 (MR_N)
unnamed: J3102.2, Q3101.3 (D), R3106.1, U3101.12 (2C)
unnamed: J4201.3, R4201.2
unnamed: J4201.4, R4204.2
unnamed: JP301.1 (A), U301.13 (SHDN_N)
unnamed: L1401.1, U1401.1 (SW), U1401.2 (SW), U1401.3 (SW)
unnamed: L1402.1, U1402.1 (SW), U1402.2 (SW), U1402.3 (SW)
unnamed: L1403.1, U1403.1 (SW), U1403.2 (SW), U1403.3 (SW)
unnamed: L1501.1, U1501.1 (SW), U1501.2 (SW), U1501.3 (SW)
unnamed: L1601.1, U1601.1 (SW), U1601.2 (SW), U1601.3 (SW)
unnamed: Q301.1 (G), R302.1, R304.2
unnamed: Q302.3 (D), Q303.1 (G), U301.4 (B_GATE)
unnamed: Q302.1 (G), U301.5 (DRV)
unnamed: C302.1, Q303.2 (D), U301.1 (IN), U301.2 (IN), U301.3 (IN)
unnamed: Q1903.3 (D), R1906.2
unnamed: Q1907.3 (D), R1907.2, R1909.2
unnamed: Q2001.3 (D), R2009.2, R2011.2
unnamed: R307.2, R314.1
unnamed: R310.2, R313.1
unnamed: R316.2, R318.1
unnamed: R2101.1, R2102.1, R2103.2
unnamed: R4504.1, R4505.1
unnamed: R315.1, U301.11 (ILIM)
unnamed: R306.1, R314.2, U301.16 (PGTH)
unnamed: C304.1, U301.10 (dVdT)
unnamed: C1312.2, U1301.1 (BOOT)
unnamed: C1305.1, U1301.14 (SS)
unnamed: C1402.1, U1401.9 (SS/TR)
unnamed: C1406.1, U1402.9 (SS/TR)
unnamed: C1411.1, U1403.9 (SS/TR)
unnamed: C1504.1, U1501.9 (SS/TR)
unnamed: C1603.1, U1601.9 (SS/TR)
unnamed: C1704.1, U1701.8 (NR/SS)
unnamed: C1707.1, U1702.8 (NR/SS)
unnamed: R1903.2, U1901.1 (A)
unnamed: R2002.2, U2001.1 (A)
unnamed: R2003.2, U2002.1 (A)
unnamed: R2010.2, U2002.4 (C)
unnamed: R2005.2, U2003.1 (A)
unnamed: C3805.1, R3801.2, R3809.1, U3801.4 (IN1-)
unnamed: C3801.1, R3805.1, R3807.2, U3801.6 (IN2-)
unnamed: C3804.1, R3804.2, R3810.1, U3801.8 (IN3-)
unnamed: C3803.1, R3803.1, R3806.2, U3801.10 (IN4-)
unnamed: C4101.1, R4102.1, R4103.2, U4101.5 (IN1+)
unnamed: R4406.2, R4407.1, U4401.3 (IN+_A)
unnamed: R4401.2, R4405.2, U4401.2 (IN-_A)
unnamed: R4403.2, R4409.2, U4401.6 (IN-_B)
unnamed: R4401.1, R4402.1, R4404.1, U4401.1 (OUT_A)
unnamed: R4403.1, R4408.1, U4401.7 (OUT_B)
unnamed: R4506.1, U4501.3 (LIMIT)
unnamed: R4516.2, U4501.2 (OUT)
unnamed: R4507.1, U4502.3 (LIMIT)
unnamed: R4514.2, U4502.2 (OUT)
unnamed: R4512.1, U4503.1 (OUT)
unnamed: R4510.1, U4504.3 (LIMIT)
unnamed: R4511.2, U4504.2 (OUT)
unnamed: R4610.1, U4601.3 (LIMIT)
unnamed: R4604.2, U4601.2 (OUT)
unnamed: R4605.1, U4602.3 (LIMIT)
unnamed: R4601.2, U4602.2 (OUT)
unnamed: R4609.1, U4603.3 (LIMIT)
unnamed: R4611.2, U4603.2 (OUT)
unnamed: R4712.1, U4701.3 (LIMIT)
unnamed: R4701.2, U4701.2 (OUT)
unnamed: R4706.1, U4702.3 (LIMIT)
unnamed: R4711.2, U4702.2 (OUT)
unnamed: R4709.1, U4703.3 (LIMIT)
unnamed: R4715.2, U4703.2 (OUT)
unnamed: R4716.1, U4704.3 (LIMIT)
unnamed: R4714.2, U4704.2 (OUT)
unnamed: R4803.1, U4801.3 (LIMIT)
unnamed: R4802.2, U4801.2 (OUT)
unnamed: R4806.1, U4802.3 (LIMIT)
unnamed: R4807.2, U4802.2 (OUT)
unnamed: R4815.1, U4803.3 (LIMIT)
unnamed: R4812.2, U4803.2 (OUT)
unnamed: R4801.1, U4804.3 (LIMIT)
unnamed: R4814.2, U4804.2 (OUT)
unnamed: R5303.1, U5301.1 (OUT_A), U5301.2 (IN-_A)
unnamed: R5305.1, U5301.6 (IN-_B), U5301.7 (OUT_B)
OC_I_N15: D4402.3 (K1/A2), R4404.2, U4101.4 (IN1-)
OC_OK_N: R4101.2, R5302.1, U2601.44 (PA12), U3101.10 (2B), U4101.2 (OUT1), U4501.6 (~ALERT), U4502.6 (~ALERT), U4504.6 (~ALERT), U4601.6 (~ALERT), U4602.6 (~ALERT), U4603.6 (~ALERT), U4701.6 (~ALERT), U4702.6 (~ALERT), U4703.6 (~ALERT), U4704.6 (~ALERT), U4801.6 (~ALERT), U4802.6 (~ALERT), U4803.6 (~ALERT), U4804.6 (~ALERT)
P15: J2401.1, J2401.3, J2402.1, Q1904.3 (D), R1001.1, R1002.2, R1004.2, R4606.2, U4601.7 (IN-)
P15_RAW: C1002.1, C1003.1, C1005.1, C1007.1, C1010.1, L1001.2, R1002.1, R1005.1, U4601.8 (IN+)
P15_SW: C1006.2, L1001.1, U1001.8 (SW)
P15_VCC: C1009.1, U1001.6 (VCC)
PGR_ANA5: R1706.1, U1701.5 (PG), U2601.63 (PB9), U3902.10 (2B)
PGR_ANA33: R1711.1, U1702.5 (PG), U2601.64 (PC10), U3902.12 (2C)
PGR_AUX18: R1406.1, U1401.4 (PG), U2601.57 (PB3), U3701.3 (B), U3901.13 (2D)
PGR_AUX25: R1411.1, U1402.4 (PG), U2601.58 (PB4), U3902.1 (1A)
PGR_CORE: R1301.1, U1301.16 (PGOOD), U2601.56 (PD6), U3901.12 (2C)
PGR_DDR: R1506.1, U1501.4 (PG), U2601.60 (PB6), U3902.4 (1C)
PGR_IO18: R1604.1, U1601.4 (PG), U2601.61 (PB7), U3902.5 (1D)
PGR_IO33: R1416.1, U1403.4 (PG), U2601.59 (PB5), U3902.2 (1B)
PGR_VTT: R1509.1, U1502.9 (PGOOD), U2601.62 (PB8), U3902.9 (2A)
PG_ANA: R3808.1, U2601.53 (PD3), U3801.1 (OUT2), U3901.5 (1D)
PG_FPGA: R802.2, U801.16 (PGOOD), U2601.52 (PD2), U3901.4 (1C)
PG_INPUT: R311.1, U301.17 (PGOOD), U2601.42 (PA10), U3101.4 (1C)
PG_N15: R3802.1, U2601.55 (PD5), U3801.13 (OUT4), U3901.10 (2B)
PG_P15: R3811.1, U2601.54 (PD4), U3801.14 (OUT3), U3901.9 (2A)
PG_SYS: R701.2, U701.16 (PGOOD), U2601.51 (PD1), U3901.1 (1A), U3901.2 (1B)
PG_USB: R3812.1, U2601.50 (PD0), U3801.2 (OUT1)
PM_RESET_N: C2703.1, D2701.3 (A1/A2), J4201.5, R2702.1, U2601.12 (PF2/NRST), U3101.13 (2D)
PM_SWCLK_MCU: R4204.1, R4206.1, U2601.46 (PA14/BOOT0/SWCLK)
PM_SWDIO_MCU: R4201.1, U2601.45 (PA13/SWDIO)
PM_UART_RX: R2903.1, U2601.41 (PD9), U2902.4 (Y)
PM_UART_TX: R4207.1, U2601.40 (PD8), U4201.2 (1A)
PM_UART_TX_POWER: J2201.7, J4202.3, U4201.3 (1Y)
PM_WDI: R2706.1, U2601.15 (PC2), U2702.6 (WDI)
PM_WDO_N: D2701.2 (K2), R2705.1, U2601.16 (PC3), U2702.7 (WDO_N), U3101.2 (1B)
PROG_N15: C2002.2, C2003.1, D2004.2 (A), J2101.3, J2401.15, Q2004.3 (D), R2004.1, R2007.1, R2009.1, R2011.1
PROG_P15: C1902.2, C1903.1, D1901.1 (K), J2101.1, J2401.13, Q1901.3 (D), R1901.1, R1907.1, R1908.1, R1909.1, R2103.1
PROG_V_P15: C2101.1, D2101.3 (K1/A2), R2102.2, U2601.20 (PA3)
PWR_ARM_PULSE: R3107.1, U2601.13 (PC0), U3102.3 (1CLK)
PWR_KILL_GPIO: Q3101.1 (G), R3102.1, U2601.1 (PC11)
REFIN_VTT: C1510.1, R1507.1, R1510.2, U1502.1 (REFIN)
STARTUP_CT: R3004.2, U3001.4 (CT)
STARTUP_READY_H: U3002.4 (Y), U3003.2 (B), U3401.1 (1OE), U3401.7 (2OE), U3402.1 (1OE), U3402.7 (2OE), U3403.1 (1OE), U3403.7 (2OE), U3404.1 (1OE), U3404.7 (2OE), U3405.1 (1OE), U3405.7 (2OE), U3406.1 (1OE), U3406.7 (2OE), U3407.1 (1OE), U3407.7 (2OE), U3408.1 (1OE), U3408.7 (2OE), U5101.2 (A)
STARTUP_RESET_N: R3003.2, U3001.1 (RESET_N), U3002.2 (A)
STARTUP_SENSE: R3001.2, R3002.1, U3001.5 (SENSE)
SYS3V3: C2702.1, C4201.1, J2303.1, J2303.3, J2303.5, J4202.1, R703.1, R706.2, R2703.2, R2707.2, R4508.2, U2701.1 (VDD), U2701.5 (SET1), U4201.14 (VCC), U4502.7 (IN-)
SYS_BOOT: C714.1, U701.6 (BOOT)
SYS_RAW: C701.2, C702.2, C706.2, C709.2, C710.2, C711.2, C712.2, C713.2, L701.2, R704.2, R706.1, U701.9 (BIAS), U4502.8 (IN+)
SYS_SS: C703.2, U701.11 (SS/TRK)
SYS_VCC: C704.2, U701.8 (VCC)
USB5: J2304.5, J2304.7, R601.1, R604.2, R4509.2, U4501.7 (IN-)
USB_RAW: C602.2, C603.2, L601.2, R604.1, R605.2, U4501.8 (IN+)
USB_SW: C605.2, L601.1, U601.6 (SW)
VREG5_CORE: C1302.1, R1308.1, U1301.17 (VREG5)
VTT: C1505.1, C1507.1, C1508.1, J2302.7, J2302.9, R4205.1, U1502.3 (VO), U1502.5 (VOSNS)
